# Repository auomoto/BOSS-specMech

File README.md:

# BOSS specMech
**_BOSS Spectrograph Mechanicals Controls for the LCO instrument_**

One of the two BOSS spectrographs will be moved to Las Campanas Observatory (LCO). Because existing spare parts inventory is not large enough to support two separate locations, we are replacing the obsolete items on the LCO instrument with currently available parts. One item is the microcontroller board, formerly a Z-World Little Giant, that is no longer manufactured (the original spectrograph was designed in the 1990s).

The new controller is built around a Microchip Curiosity Nano ATMega 4809. The source code and electronics schematics are here.

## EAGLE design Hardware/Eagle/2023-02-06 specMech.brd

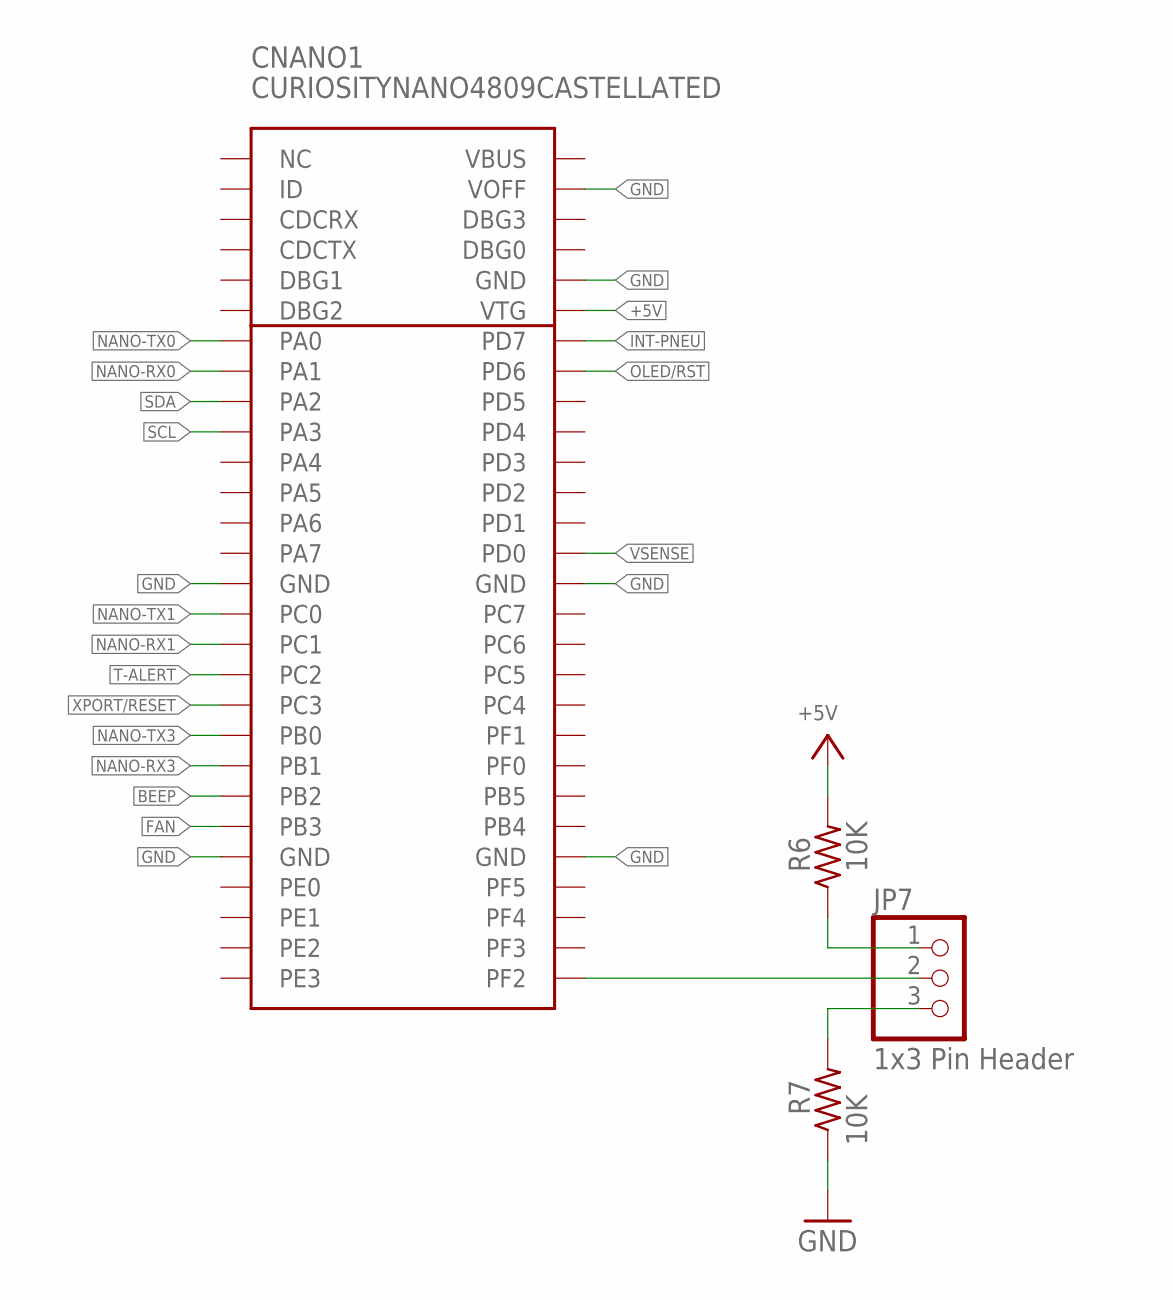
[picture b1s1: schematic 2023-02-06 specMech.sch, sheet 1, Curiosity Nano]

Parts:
CNANO1: CURIOSITYNANO4809CASTELLATED
JP7: 1x3 Pin Header; 1X03
R6, R7: 10K; R0805

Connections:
+5V: CNANO1.VTG, R6.2; also elsewhere on the board
BEEP: CNANO1.PB2; also elsewhere on the board
FAN: CNANO1.PB3; also elsewhere on the board
GND: CNANO1.GND15 (GND), CNANO1.GND24 (GND), CNANO1.GND33 (GND), CNANO1.GND42 (GND), CNANO1.GND52 (GND), CNANO1.VOFF, R7.1; also elsewhere on the board
INT-PNEU: CNANO1.PD7-AIN7 (PD7); also elsewhere on the board
unnamed: CNANO1.PF2, JP7.2
unnamed: JP7.3, R7.2
unnamed: JP7.1, R6.1
NANO-RX0: CNANO1.PA1-RX (PA1); also elsewhere on the board
NANO-RX1: CNANO1.PC1-RX (PC1); also elsewhere on the board
NANO-RX3: CNANO1.PB1-RX (PB1); also elsewhere on the board
NANO-TX0: CNANO1.PA0-TX (PA0); also elsewhere on the board
NANO-TX1: CNANO1.PC0-TX (PC0); also elsewhere on the board
NANO-TX3: CNANO1.PB0-TX (PB0); also elsewhere on the board
OLED/RST: CNANO1.PD6-AIN6 (PD6); also elsewhere on the board
SCL: CNANO1.PA3-SCL (PA3); also elsewhere on the board
SDA: CNANO1.PA2-SDA (PA2); also elsewhere on the board
T-ALERT: CNANO1.PC2; also elsewhere on the board
VSENSE: CNANO1.PD0-AIN0 (PD0); also elsewhere on the board
XPORT/RESET: CNANO1.PC3; also elsewhere on the board

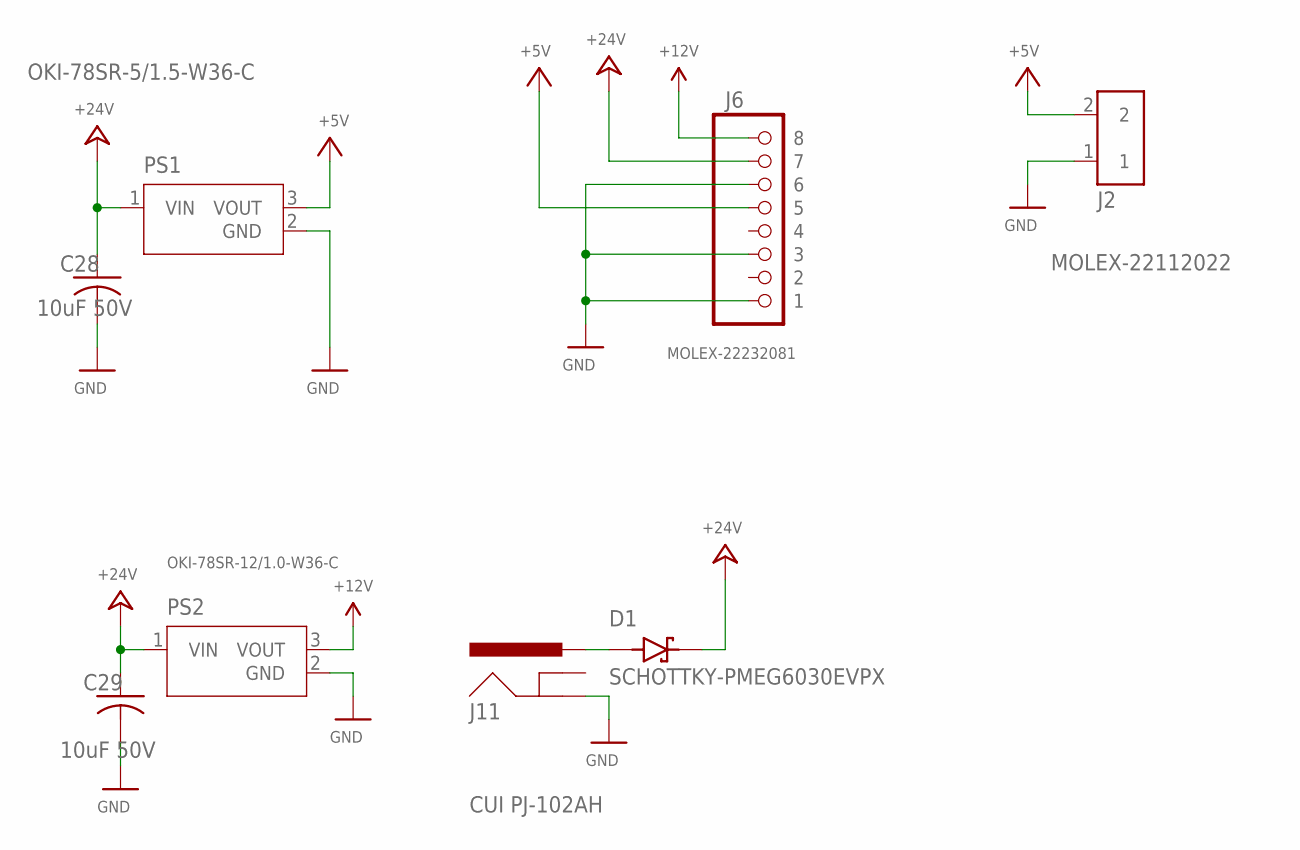
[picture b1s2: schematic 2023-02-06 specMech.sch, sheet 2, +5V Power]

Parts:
C28, C29: 10uF 50V; C1210
D1: SCHOTTKY-PMEG6030EVPX; DIO_PMEG6030EVPX
J2: MOLEX-22112022; 1X02-MOLEX-22112022
J6: MOLEX-22232081; 1X08-MOLEX-SHROUD
J11: CUI PJ-102AH; PJ-102AH
PS1: OKI-78SR-5/1.5-W36-C; CONV_OKI-78SR-5/1.5-W36-C
PS2: OKI-78SR-12/1.0-W36-C; CONV_OKI-78SR-5/1.5-W36-C

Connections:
+5V: J2.2, J6.P$5 (5), PS1.3 (VOUT); also elsewhere on the board
+12V: J6.P$8 (8), PS2.3 (VOUT); also elsewhere on the board
+24V: C28.1, C29.1, D1.1 (K), J6.P$7 (7), PS1.1 (VIN), PS2.1 (VIN); also elsewhere on the board
GND: C28.2, C29.2, J2.1, J6.P$1 (1), J6.P$3 (3), J6.P$6 (6), J11.GND, PS1.2 (GND), PS2.2 (GND); also elsewhere on the board
unnamed: D1.2 (A), J11.PWR

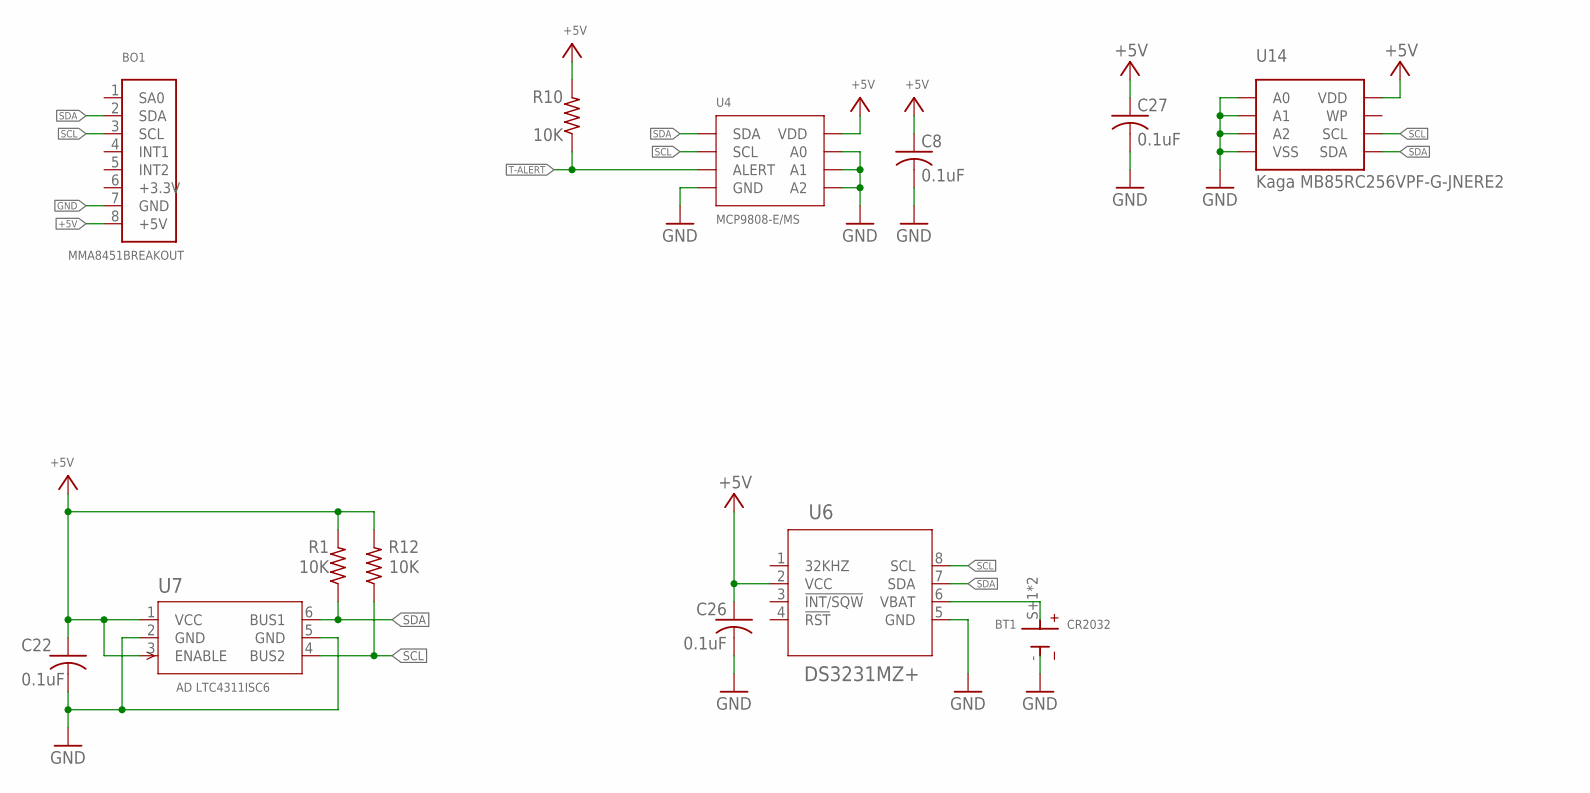
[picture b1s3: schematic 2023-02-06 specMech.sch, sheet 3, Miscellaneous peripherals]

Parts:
BO1: MMA8451BREAKOUT; 1X08
BT1: CR2032; BAT_BK-5058
C8, C22, C26, C27: 0.1uF; C0805
R1, R10, R12: 10K; R0805
U4: MCP9808-E/MS; MSOP8_MC_MCH
U6: DS3231MZ+; 21-0041B_8
U7: AD LTC4311ISC6; SOT-6_SC_LIT
U14: Kaga MB85RC256VPF-G-JNERE2; SOIC127P797X210-8N

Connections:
+5V: BO1.8 (+5V), C8.1, C22.1, C26.1, C27.1, R1.2, R10.2, R12.2, U4.8 (VDD), U6.2 (VCC), U7.1 (VCC), U7.3 (ENABLE), U14.8 (VDD); also elsewhere on the board
GND: BO1.7 (GND), BT1.-, C8.2, C22.2, C26.2, C27.2, U4.4 (GND), U4.5 (A2), U4.6 (A1), U4.7 (A0), U6.5 (GND), U7.2 (GND), U7.5 (GND), U14.1 (A0), U14.2 (A1), U14.3 (A2), U14.4 (VSS); also elsewhere on the board
SCL: BO1.3 (SCL), R12.1, U4.2 (SCL), U6.8 (SCL), U7.4 (BUS2), U14.6 (SCL); also elsewhere on the board
SDA: BO1.2 (SDA), R1.1, U4.1 (SDA), U6.7 (SDA), U7.6 (BUS1), U14.5 (SDA); also elsewhere on the board
T-ALERT: R10.1, U4.3 (ALERT); also elsewhere on the board
VBAT: BT1.S+1 (+), BT1.S+2 (+), U6.6 (VBAT)

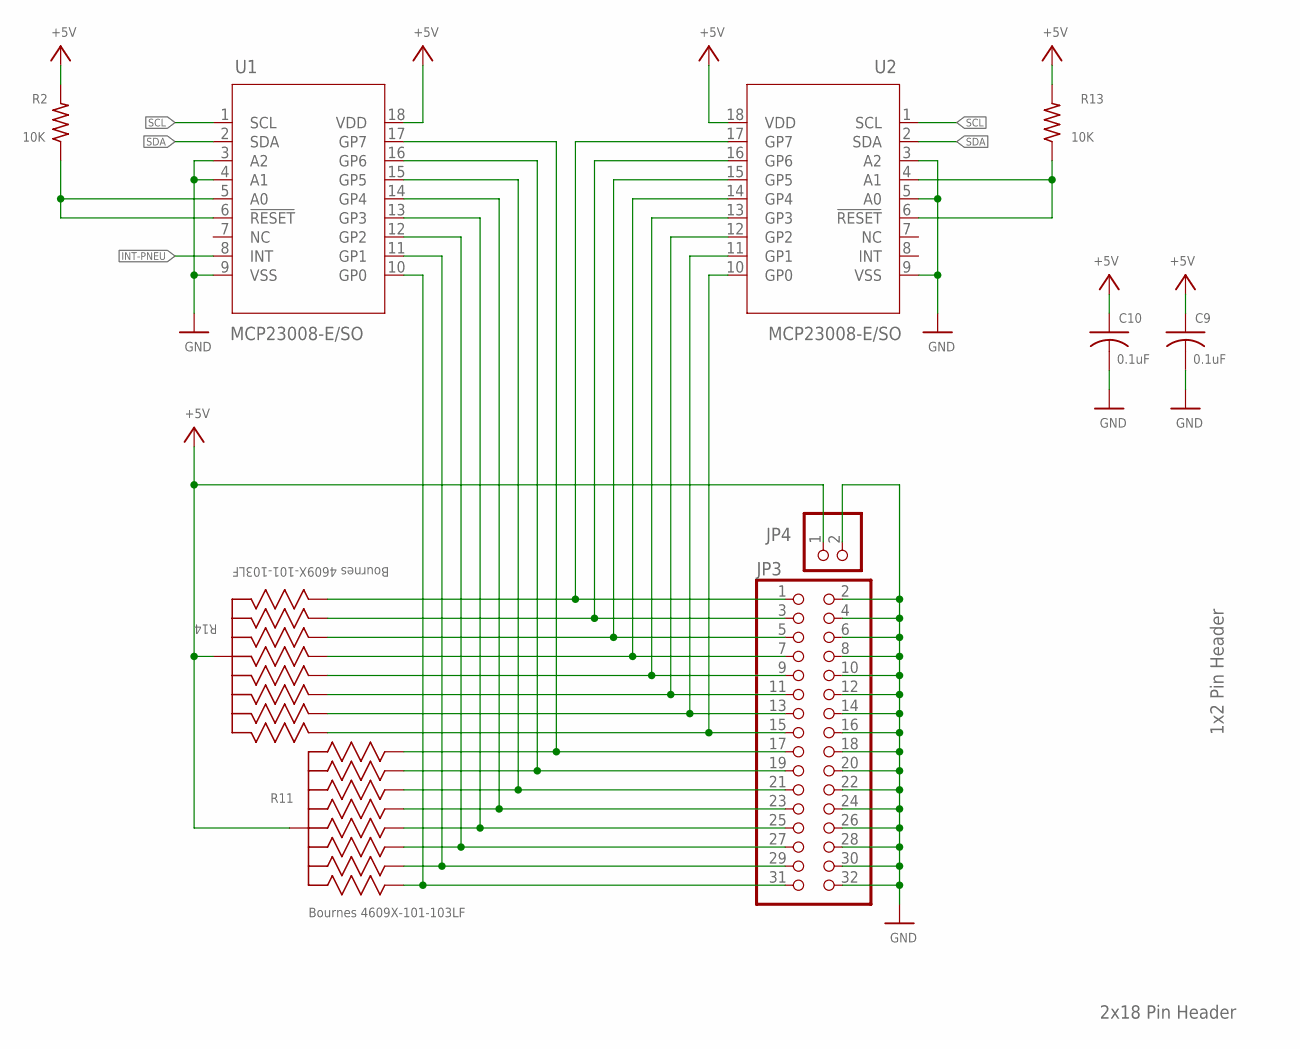
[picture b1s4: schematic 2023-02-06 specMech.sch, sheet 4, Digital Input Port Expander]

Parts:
C9, C10: 0.1uF; C0805
JP3: 2x18 Pin Header; 2X16
JP4: 1x2 Pin Header; 1X02
R2, R13: 10K; R0805
R11, R14: Bournes 4609X-101-103LF; BO_4609X
U1, U2: MCP23008-E/SO; SOIC18-W_MC

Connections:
+5V: C9.1, C10.1, JP4.1, R2.2, R11.1, R13.2, R14.1, U1.18 (VDD), U2.18 (VDD); also elsewhere on the board
GND: C9.2, C10.2, JP3.2, JP3.4, JP3.6, JP3.8, JP3.10, JP3.12, JP3.14, JP3.16, JP3.18, JP3.20, JP3.22, JP3.24, JP3.26, JP3.28, JP3.30, JP3.32, JP4.2, U1.3 (A2), U1.4 (A1), U1.9 (VSS), U2.3 (A2), U2.5 (A0), U2.9 (VSS); also elsewhere on the board
INT-PNEU: U1.8 (INT); also elsewhere on the board
unnamed: JP3.1, R14.2, U2.17 (GP7)
unnamed: JP3.3, R14.3, U2.16 (GP6)
unnamed: JP3.5, R14.4, U2.15 (GP5)
unnamed: JP3.7, R14.5, U2.14 (GP4)
unnamed: JP3.17, R11.9, U1.17 (GP7)
unnamed: JP3.19, R11.8, U1.16 (GP6)
unnamed: JP3.21, R11.7, U1.15 (GP5)
unnamed: JP3.23, R11.6, U1.14 (GP4)
unnamed: JP3.25, R11.5, U1.13 (GP3)
unnamed: R2.1, U1.5 (A0), U1.6 (!RESET)
unnamed: JP3.29, R11.3, U1.11 (GP1)
unnamed: JP3.31, R11.2, U1.10 (GP0)
unnamed: JP3.11, R14.7, U2.12 (GP2)
unnamed: JP3.27, R11.4, U1.12 (GP2)
unnamed: JP3.13, R14.8, U2.11 (GP1)
unnamed: JP3.15, R14.9, U2.10 (GP0)
unnamed: R13.1, U2.4 (A1), U2.6 (!RESET)
unnamed: JP3.9, R14.6, U2.13 (GP3)
SCL: U1.1 (SCL), U2.1 (SCL); also elsewhere on the board
SDA: U1.2 (SDA), U2.2 (SDA); also elsewhere on the board

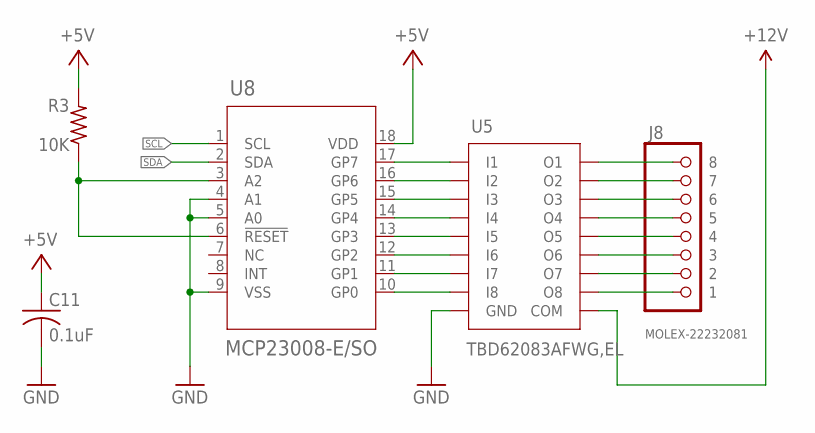
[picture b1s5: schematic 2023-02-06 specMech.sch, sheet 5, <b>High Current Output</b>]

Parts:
C11: 0.1uF; C0805
J8: MOLEX-22232081; 1X08-MOLEX-SHROUD
R3: 10K; R0805
U5: TBD62083AFWG,EL; SOIC127P1030X245-18
U8: MCP23008-E/SO; SOIC18-W_MC

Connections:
+5V: C11.1, R3.2, U8.18 (VDD); also elsewhere on the board
+12V: U5.10 (COM); also elsewhere on the board
GND: C11.2, U5.9 (GND), U8.4 (A1), U8.5 (A0), U8.9 (VSS); also elsewhere on the board
unnamed: U5.1 (I1), U8.17 (GP7)
unnamed: U5.2 (I2), U8.16 (GP6)
unnamed: U5.3 (I3), U8.15 (GP5)
unnamed: U5.4 (I4), U8.14 (GP4)
unnamed: U5.5 (I5), U8.13 (GP3)
unnamed: U5.6 (I6), U8.12 (GP2)
unnamed: U5.7 (I7), U8.11 (GP1)
unnamed: U5.8 (I8), U8.10 (GP0)
unnamed: R3.1, U8.3 (A2), U8.6 (!RESET)
unnamed: J8.P$8 (8), U5.18 (O1)
unnamed: J8.P$1 (1), U5.11 (O8)
unnamed: J8.P$2 (2), U5.12 (O7)
unnamed: J8.P$3 (3), U5.13 (O6)
unnamed: J8.P$4 (4), U5.14 (O5)
unnamed: J8.P$5 (5), U5.15 (O4)
unnamed: J8.P$6 (6), U5.16 (O3)
unnamed: J8.P$7 (7), U5.17 (O2)
SCL: U8.1 (SCL); also elsewhere on the board
SDA: U8.2 (SDA); also elsewhere on the board

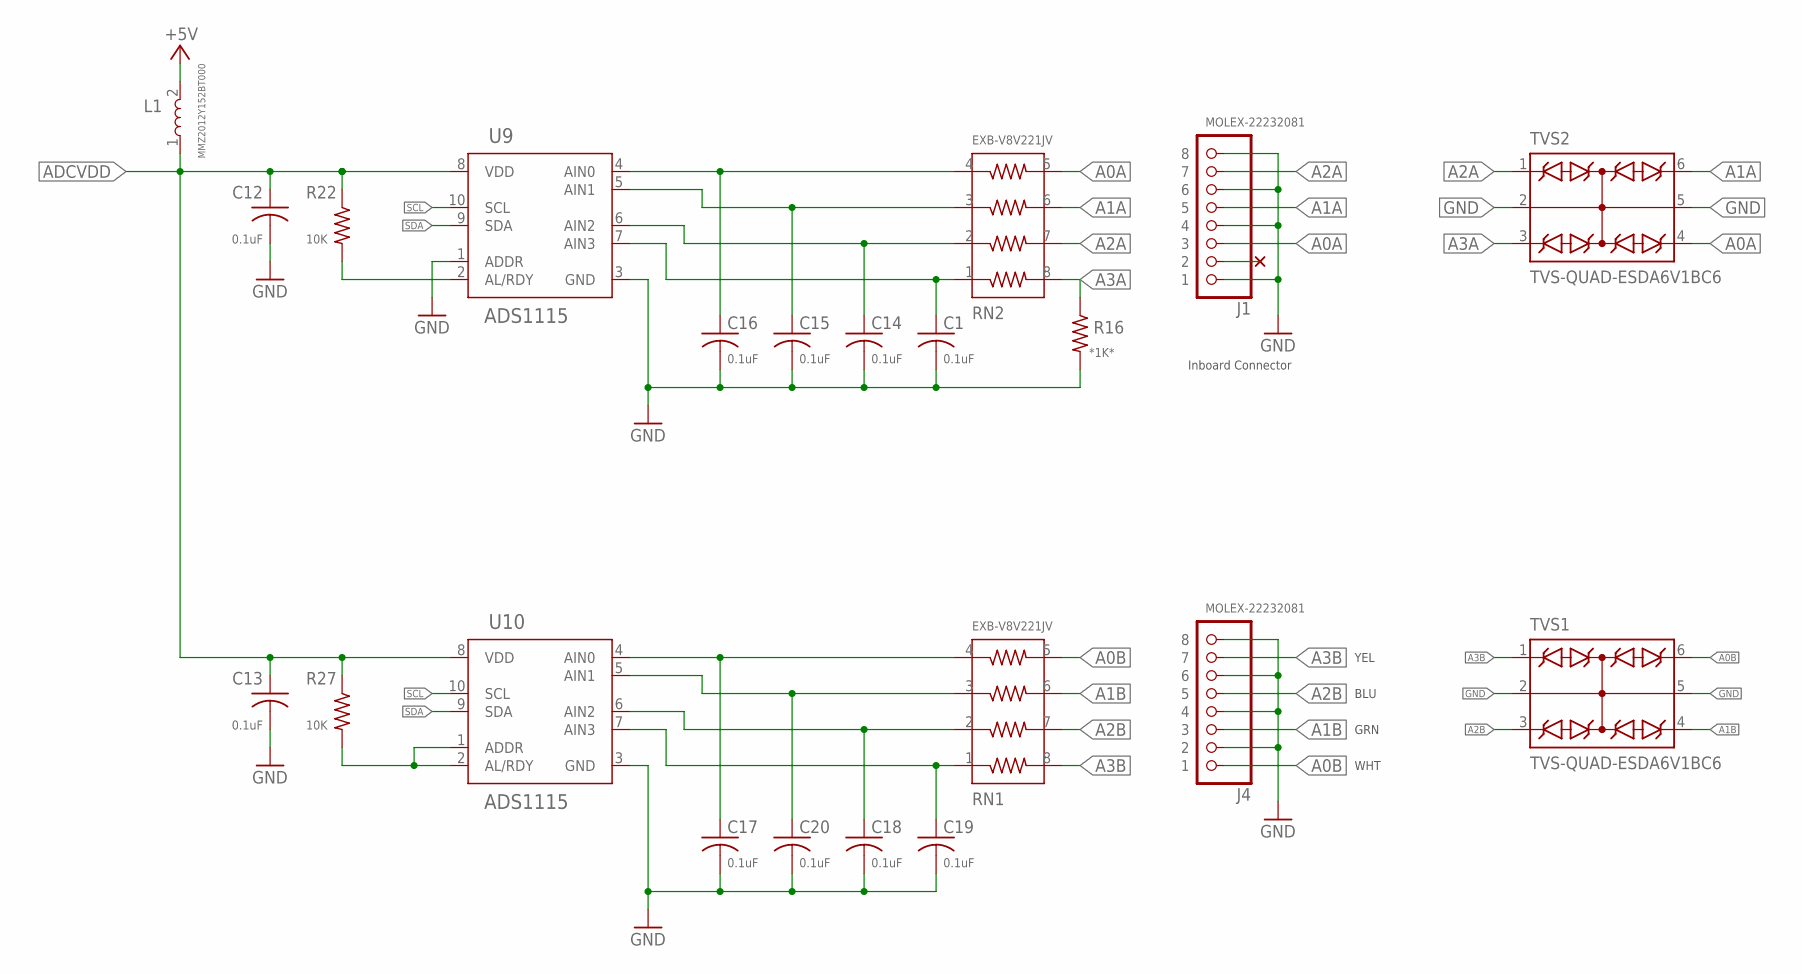
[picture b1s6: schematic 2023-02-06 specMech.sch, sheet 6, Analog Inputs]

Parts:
C1, C12, C13, C14, C15, C16, C17, C18, C19, C20: 0.1uF; C0805
J1, J4: MOLEX-22232081; 1X08-MOLEX-SHROUD
L1: MMZ2012Y152BT000; INDC2012X87N
R16: *1K*; R0805
R22, R27: 10K; R0805
RN1, RN2: EXB-V8V221JV; EXB38V_PAN
TVS1, TVS2: TVS-QUAD-ESDA6V1BC6; SOT95P280X145-6N
U9, U10: ADS1115; SOP50P490X110-10N

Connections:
+5V: L1.2; also elsewhere on the board
A0A: J1.P$3 (3), RN2.5, TVS2.4 (C3)
A0B: J4.P$1 (1), RN1.5, TVS1.6 (C4)
A1A: J1.P$5 (5), RN2.6, TVS2.6 (C4)
A1B: J4.P$3 (3), RN1.6, TVS1.4 (C3)
A2A: J1.P$7 (7), RN2.7, TVS2.1 (C1)
A2B: J4.P$5 (5), RN1.7, TVS1.3 (C2)
A3A: R16.1, RN2.8, TVS2.3 (C2); also elsewhere on the board
A3B: J4.P$7 (7), RN1.8, TVS1.1 (C1)
ADCVDD: C12.1, C13.1, L1.1, R22.1, R27.1, U9.8 (VDD), U10.8 (VDD); also elsewhere on the board
GND: C1.2, C12.2, C13.2, C14.2, C15.2, C16.2, C17.2, C18.2, C19.2, C20.2, J1.P$1 (1), J1.P$4 (4), J1.P$6 (6), J1.P$8 (8), J4.P$2 (2), J4.P$4 (4), J4.P$6 (6), J4.P$8 (8), R16.2, TVS1.2 (CC1), TVS1.5 (CC2), TVS2.2 (CC1), TVS2.5 (CC2), U9.1 (ADDR), U9.3 (GND), U10.3 (GND); also elsewhere on the board
unnamed: C1.1, RN2.1, U9.7 (AIN3)
unnamed: C16.1, RN2.4, U9.4 (AIN0)
unnamed: C15.1, RN2.3, U9.5 (AIN1)
unnamed: R22.2, U9.2 (AL/RDY)
unnamed: C19.1, RN1.1, U10.7 (AIN3)
unnamed: C14.1, RN2.2, U9.6 (AIN2)
unnamed: C18.1, RN1.2, U10.6 (AIN2)
unnamed: C20.1, RN1.3, U10.5 (AIN1)
unnamed: C17.1, RN1.4, U10.4 (AIN0)
unnamed: R27.2, U10.1 (ADDR), U10.2 (AL/RDY)
SCL: U9.10 (SCL), U10.10 (SCL); also elsewhere on the board
SDA: U9.9 (SDA), U10.9 (SDA); also elsewhere on the board

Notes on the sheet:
WHT
GRN
YEL
BLU
Inboard Connector

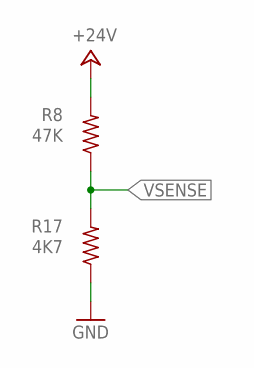
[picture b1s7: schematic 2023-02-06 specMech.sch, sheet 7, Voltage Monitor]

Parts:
R8: 47K; R0805
R17: 4K7; R0805

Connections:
+24V: R8.2; also elsewhere on the board
GND: R17.1; also elsewhere on the board
VSENSE: R8.1, R17.2; also elsewhere on the board

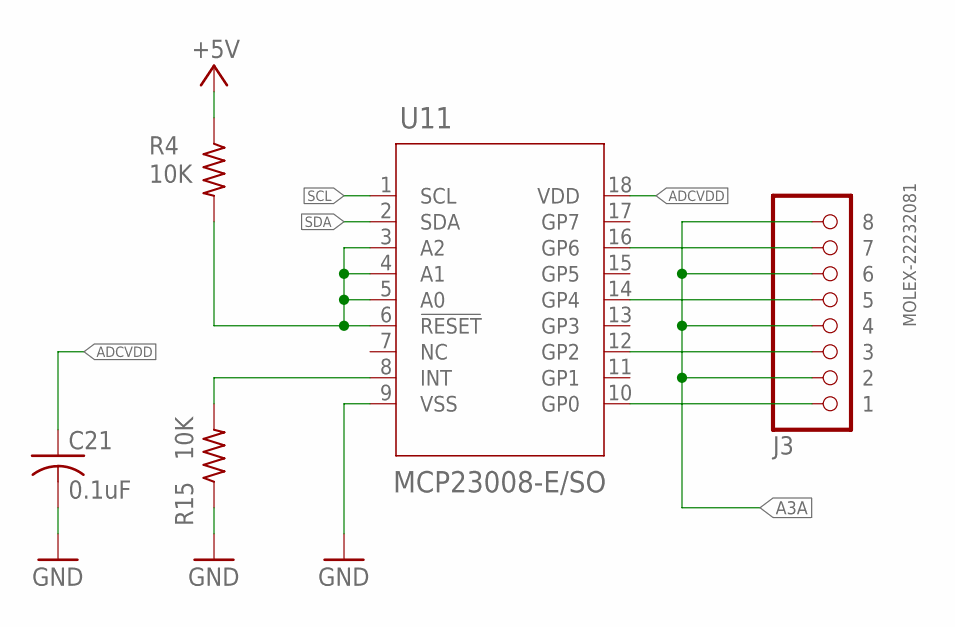
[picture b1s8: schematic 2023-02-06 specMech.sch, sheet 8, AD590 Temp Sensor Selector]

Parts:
C21: 0.1uF; C0805
J3: MOLEX-22232081; 1X08-MOLEX-SHROUD
R4, R15: 10K; R0805
U11: MCP23008-E/SO; SOIC18-W_MC

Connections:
+5V: R4.1; also elsewhere on the board
A3A: J3.P$2 (2), J3.P$4 (4), J3.P$6 (6), J3.P$8 (8); also elsewhere on the board
ADCVDD: C21.1, U11.18 (VDD); also elsewhere on the board
GND: C21.2, R15.1, U11.9 (VSS); also elsewhere on the board
unnamed: R4.2, U11.3 (A2), U11.4 (A1), U11.5 (A0), U11.6 (!RESET)
unnamed: R15.2, U11.8 (INT)
unnamed: J3.P$1 (1), U11.10 (GP0)
unnamed: J3.P$3 (3), U11.12 (GP2)
unnamed: J3.P$5 (5), U11.14 (GP4)
unnamed: J3.P$7 (7), U11.16 (GP6)
SCL: U11.1 (SCL); also elsewhere on the board
SDA: U11.2 (SDA); also elsewhere on the board

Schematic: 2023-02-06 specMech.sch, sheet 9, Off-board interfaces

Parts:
C2, C3, C23, C24, C25: 0.1uF; C0805
C4, C5: 0.01uF; C0805
C6: 10uF 50V; C1210
C7: 10uF 6V3; C0805
J7: Lantronix XPORT; XPORT-2
J9, J10: MOLEX-22112022; 1X02-MOLEX-22112022
J12: MOLEX-22112062; 1X06-MOLEX-22112062
JP1: 2x5 Pin Header; 2X05
JP2, JP5: 1x2 Pin Header; 1X02
JP6: Amphenol 75869-131LF; PINHD-2X3-SHROUDED
R5, R9: 10K; R0805
U3: TXB0102DCURVSSOP8; GHI-IC_VSSOP8(TI)
U12: 74HC2G17SOT457; SOP95P275X110-6
U13: ISO7421DR; SOIC127P599X175-8N
U15: SN74LV1T34DBVR; SOT95P280X145-5N
VR2: P7805-Q24-S3-S; CONV_P7805-Q24-S3-S

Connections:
+3.3V: C2.1, C4.1, C7.1, J7.3.3V (+3.3V), R9.2, U3.3 (VCCA), U15.5 (VCC), VR2.VOUT
+5V: C3.1, C23.1, C25.1, J12.6, JP1.8, JP2.2, JP6.3, U3.7 (VCCB), U12.5 (VCC), U13.8 (VCC2); also elsewhere on the board
+24V: C6.1, JP1.1, VR2.VIN; also elsewhere on the board
BEEP: J10.2; also elsewhere on the board
COLL-RX: JP1.3, U12.6 (1Y)
COLL-TX: JP1.7, U12.3 (2A)
CP3: J7.CP1, J7.CP2, J7.CP3, R5.2
FAN: J9.2; also elsewhere on the board
GND: C2.2, C3.2, C5.1, C6.2, C7.2, C23.2, C25.2, J7.GND, J9.1, J10.1, J12.5, JP1.2, JP1.5, JP1.9, JP5.2, JP6.2, JP6.5, R5.1, U3.2 (GND), U12.2 (GND), U13.5 (GND2), U15.3 (GND), VR2.GND; also elsewhere on the board
GND1: C24.2, J12.2, JP5.1, U13.4 (GND1)
GND-1: C4.2, C5.2, J7.P$1 (SH1), J7.P$2 (SH2)
INB: J12.1, U13.3 (INB)
unnamed: R9.1, U3.6 (OE)
NANO-RX0: U3.8 (B1); also elsewhere on the board
NANO-RX1: U12.4 (2Y); also elsewhere on the board
NANO-RX3: U13.6 (OUTB); also elsewhere on the board
NANO-TX0: U3.1 (B2); also elsewhere on the board
NANO-TX1: U12.1 (1A); also elsewhere on the board
NANO-TX3: U13.7 (INA); also elsewhere on the board
OLED/RST: JP6.4; also elsewhere on the board
OUTA: J12.3, U13.2 (OUTA)
SCL: JP6.6; also elsewhere on the board
SDA: JP6.1; also elsewhere on the board
VCC1: C24.1, J12.4, JP2.1, U13.1 (VCC1)
XP-RX: J7.RX, U3.4 (A2)
XP-TX: J7.TX, U3.5 (A1)
XP/RST: J7./RST, U15.4 (Y)
XPORT/RESET: U15.2 (A); also elsewhere on the board

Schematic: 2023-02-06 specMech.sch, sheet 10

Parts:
TP1, TP5: TP5000-TESTPOINT-BLK
TP2: TP5000-TESTPOINT-RED
TP3: TP5000-TESTPOINT-BLU
TP4: TP5000-TESTPOINT-YEL
TP6, TP7: TP5000-TESTPOINT-ORG

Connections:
+5V: TP2.P$1; also elsewhere on the board
+24V: TP6.P$1; also elsewhere on the board
GND: TP1.P$1, TP5.P$1; also elsewhere on the board
SCL: TP4.P$1; also elsewhere on the board
SDA: TP3.P$1; also elsewhere on the board
VSENSE: TP7.P$1; also elsewhere on the board

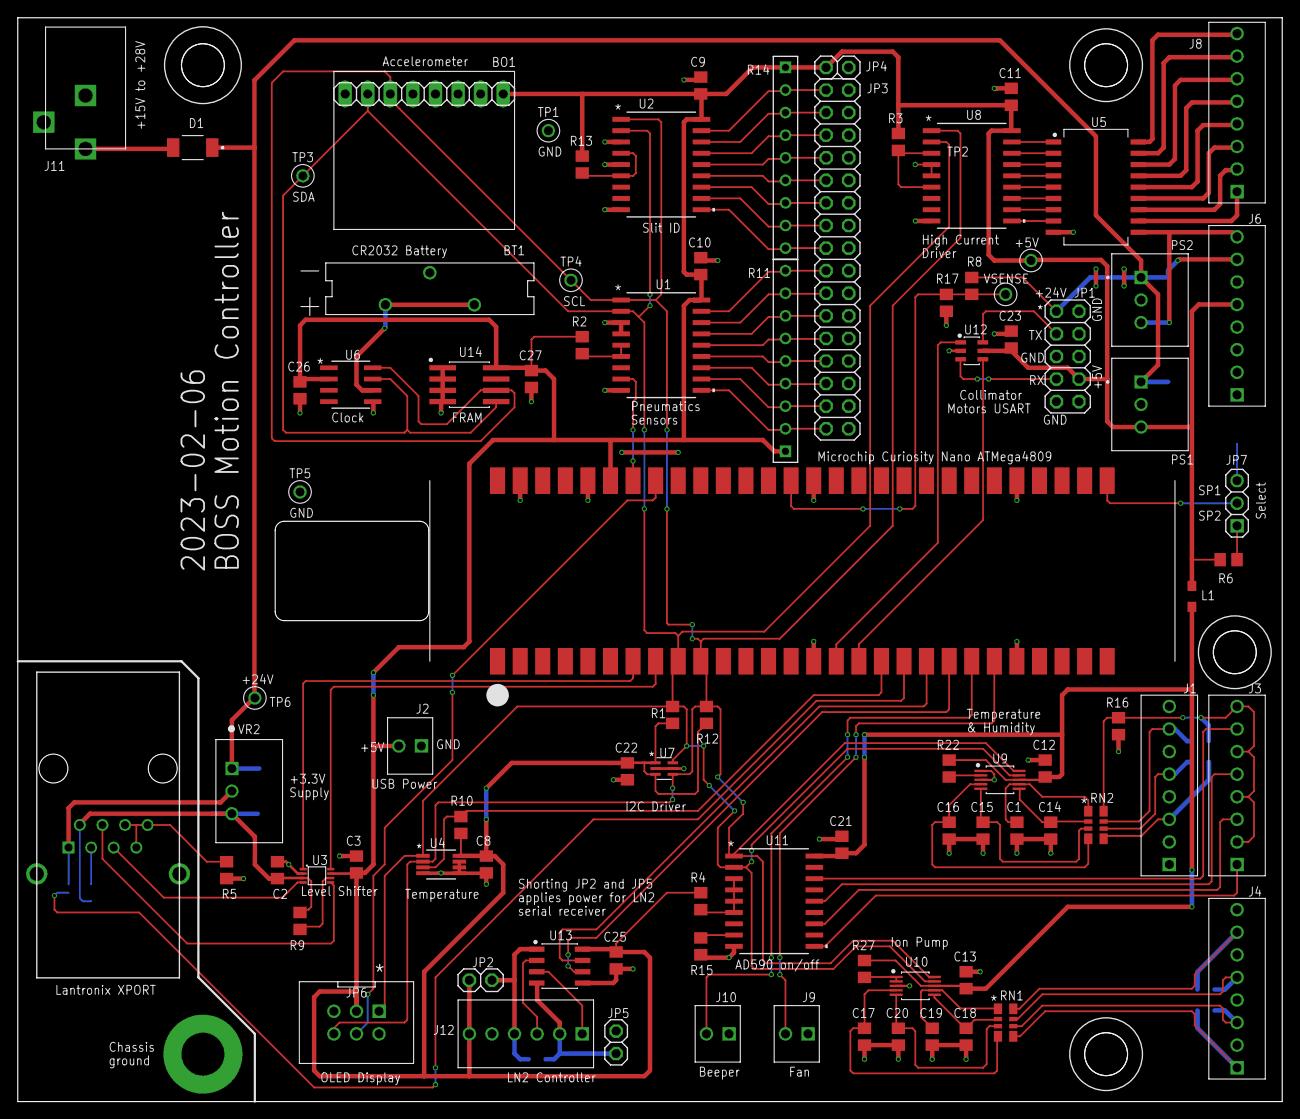
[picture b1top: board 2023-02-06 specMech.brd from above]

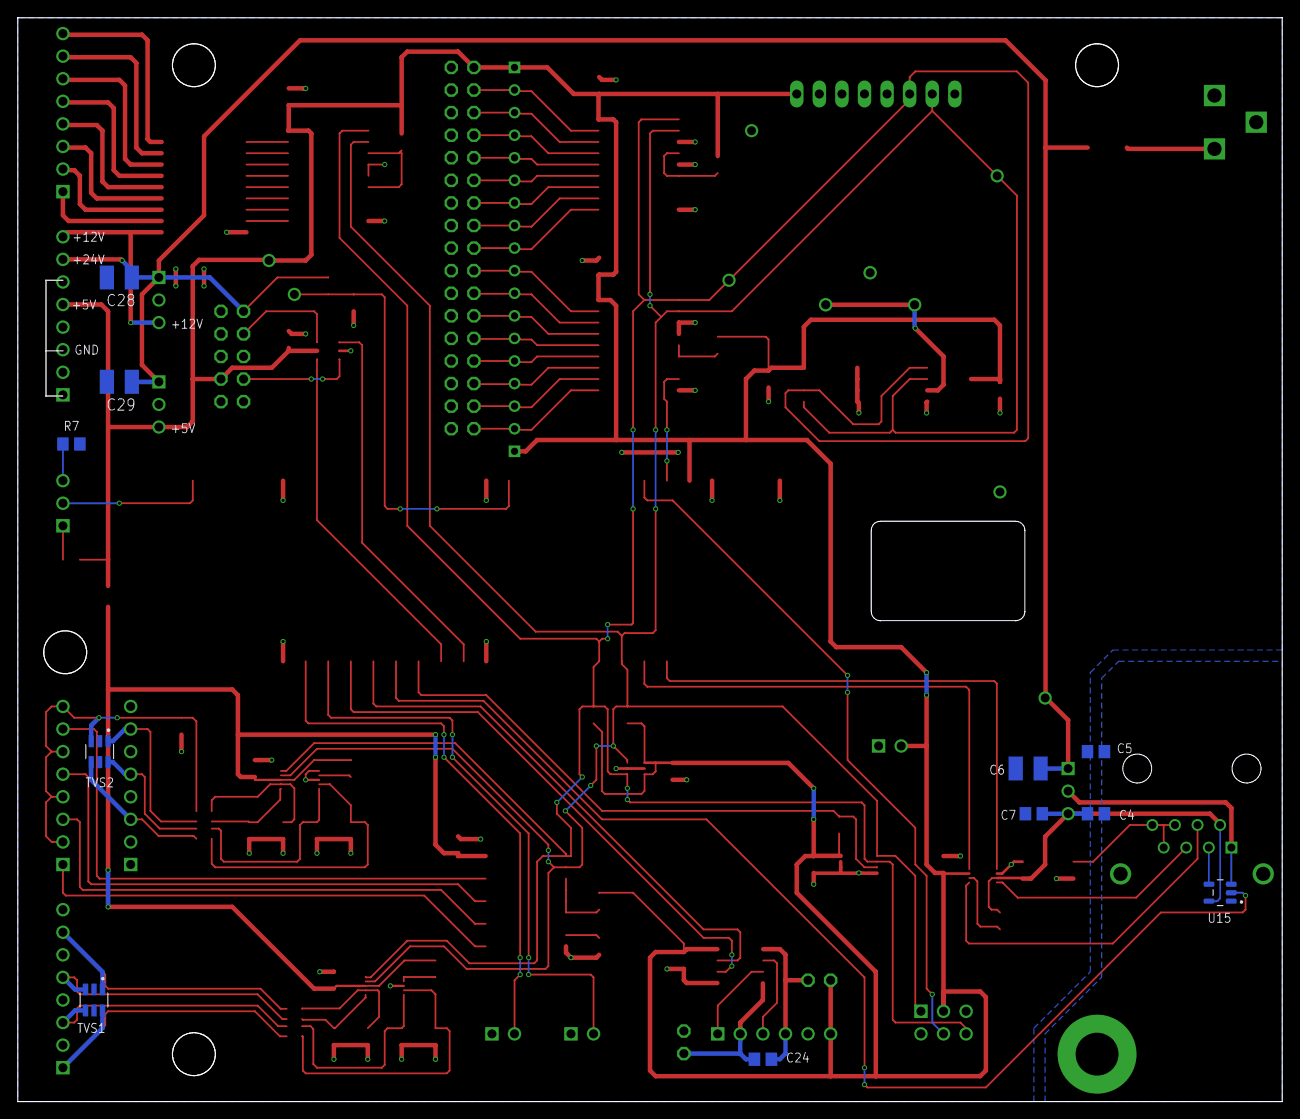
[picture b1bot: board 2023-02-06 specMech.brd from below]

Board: 2 copper layers, 142.2 x 121.9 mm, 100 parts (11 on the bottom side), 97 nets.

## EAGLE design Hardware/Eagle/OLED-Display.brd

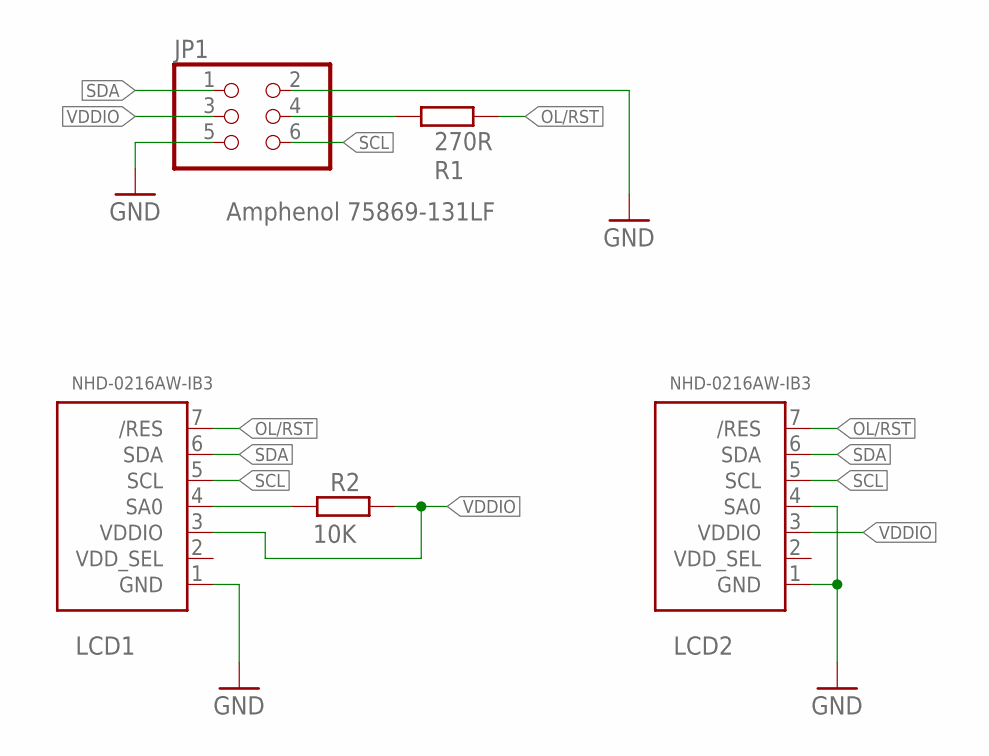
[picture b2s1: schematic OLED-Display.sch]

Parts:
JP1: Amphenol 75869-131LF; PINHD-2X3-SHROUDED
LCD1, LCD2: NHD-0216AW-IB3; LCD-NEWHAVEN-16X2
R1: 270R; R0805
R2: 10K; R0805

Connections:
ADDR1: LCD1.4 (SA0), R2.1
GND: JP1.2, JP1.5, LCD1.1 (GND), LCD2.1 (GND), LCD2.4 (SA0)
OL/RST: LCD1.7 (/RES), LCD2.7 (/RES), R1.2
RESET: JP1.4, R1.1
SCL: JP1.6, LCD1.5 (SCL), LCD2.5 (SCL)
SDA: JP1.1, LCD1.6 (SDA), LCD2.6 (SDA)
VDDIO: JP1.3, LCD1.3 (VDDIO), LCD2.3 (VDDIO), R2.2

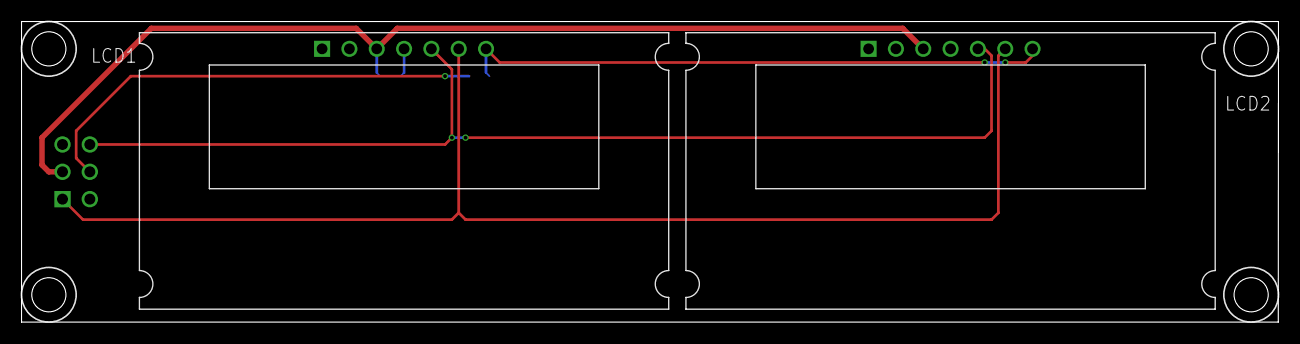
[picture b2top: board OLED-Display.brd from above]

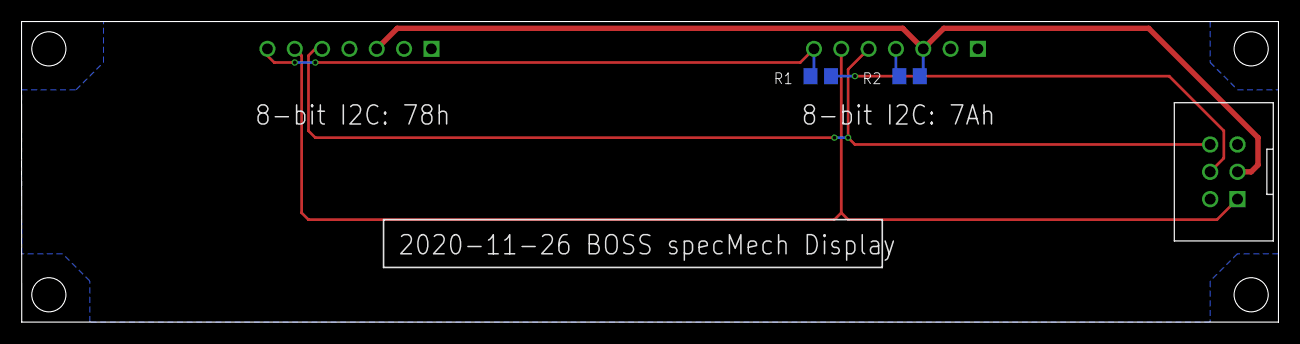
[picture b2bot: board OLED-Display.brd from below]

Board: 2 copper layers, 116.8 x 27.9 mm, 5 parts (3 on the bottom side), 7 nets.

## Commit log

2020-10-19 BOSS Mechanical Controls
    Atmel Studio 7 software runs on a Curiosity Nano ATMega4809 to control the BOSS spectrograph mechanical items and sensors.
2020-10-19 specMech
    BOSS spectrograph mechanicals software
2020-10-19 Set theme jekyll-theme-slate
2020-10-19 Set theme jekyll-theme-minimal
2020-10-19 removed theme
2020-10-19 Added Eagle schematic and board files
    These are far from final.
2020-10-21 Worked on board layout
2020-10-26 Remove backup Eagle files
2020-10-27 Started XPORT placement
2020-10-28 Fixed level shifter orientation
2020-10-29 Change name to include BOSS
2020-10-30 Added Schmitt trigger to RoboClaw interface
2020-10-30 Added RTC & battery
2020-10-30 Rearranged parts on board
2020-11-01 Removed XPORT hole over pad, general cleanup
2020-11-01 ADC area layout improvements
2020-11-01 Add shorting jumper to ADC ground
2020-11-01 Removed errant character at end of brd file
2020-11-01 Rearrange ADC chips after brd file recovery
2020-11-01 Rearranging parts
2020-11-01 Added ADC ground plane
2020-11-01 Routed high current lines
2020-11-01 Wiring
2020-11-04 Fixed accelerometer footprint
2020-11-04 Connected pneumatic sensor interrupt
2020-11-04 Added Ground Overpasses
2020-11-04 Moved wire for USB port clearance on Nano board
2020-11-06 Partitioned grounds (removed analog ground)
2020-11-06 Updated board label
2020-11-06 Enlarged USB connector clearance hole
2020-11-06 Problem pushing to fusion
2020-11-06 Reverting to change label time
2020-11-06 Used later version of XPORT-2
2020-11-07 Finish for the day
2020-11-07 Connected VOFF to GND
2020-11-09 Added +5V power for USB isolator (JST 2-pin header)
2020-11-09 Changed FRAM footprint to allow both IC sizes
2020-11-10 Added spectrograph selection jumper
2020-11-10 Fixed label errors in humidity sensor input lines
2020-11-10 Added test points, changed conflicting i2c address
2020-11-11 Added some part values, changed date on label
2020-11-11 Added cutout for USB connector, cleaned up some traces
2020-11-12 Submitted this one (Rev0) for fab to Oshpark
    2020-11-12 specMech Rev0
2020-11-18 Moved shim thickness text
2020-11-18 Added future change notes to schematic
2020-11-19 Removed old backup files
2020-11-26 Added OLED-Display
2020-11-27 Added pullup note to schematic
2020-12-12 Printed 2020-11-12 Schematic
2020-12-15 Made copy of 2020-11-12 version
2020-12-26 Recover Github error?
2020-12-27 Removed EOD line
2020-12-27 Modified FRAM routines for new TWI code
2020-12-27 Cleaned up comments and in-line documentation
2020-12-29 Wrote ADS1115 routine, not tested
2021-01-02 Re-did the ADC and AD590 routines
2021-01-02 Commented main.c and added PROMPT defines
2021-01-02 Updated comments in all files
2021-01-04 Set up differential ADC for Ion Pump readout
2021-01-05 Cleaned up ion pump routine, verified operation
2021-01-05 Minor edits
2021-01-13 Removed timezone (Z) from reported times
2021-01-14 Updated docs to match the code
2021-01-14 Fixed formatting error in format_ERR
2021-01-19 OLED Display minor mods
2021-01-24 Removed Eagle backup files
2021-01-24 Edited comments
2021-01-25 Added command ID to the loop
    Added a command parsing routine, pulling the command pieces out into a new structure. This is to create a command identifier that can be carried with every instance of a command.
2021-01-25 Cmd loop mods for more commands
2021-01-25 Removed commented routines
2021-01-25 Removed error mesg on empty <CR>
2021-01-26 Starting major changes
    Moved ferrite bead
2021-01-26 Swapped castellated board in, starting rerouting
2021-01-26 More routing
2021-01-27 More routing, mostly OK now
2021-01-27 Molex 1x2 header replaces JST header
2021-01-27 Added TVS diodes on ADC inputs
2021-01-27 Moved the accelerometer a bit away from board edge
2021-01-31 Accelerometer small mods
2021-02-06 Started testing OLED display
2021-02-06 Enabled button to reboot
2021-02-06 Set up RTC for flashing led
2021-02-07 globals.h failure
2021-02-07 fail globals.h
2021-02-07 Recover
2021-02-07 fail
2021-02-07 Revert
2021-02-07 undoing
2021-02-08 Re-loaded everything into a new Atmel Studio project
2021-02-08 Updated part number for high current driver
2021-02-08 USB Cutout in board bigger; software debugging
2021-02-09 Pneumatics interrupt detected, display improvements
2021-02-10 Changed LN2 connector pinout to swap rx & tx
2021-02-13 Added fan control
2021-02-14 Changed to 7-bit TWI addresses everywhere
2021-02-17 Forced rebootack to be !<CR> EXACTLY
2021-02-17 Removed boottime command (rB)
2021-02-18 Added XPort reset & changed OLED display connector
2021-02-20 Added 10uF cap on 5V dc-dc input
2021-02-22 Labeled Fan connector
2021-02-22 separated uart tracks a bit
2021-02-23 Made a copy today
2021-02-24 trying to fix the hacking problem; clamped input buffer overflow
2021-02-24 Recompiled with XPort reset on reboot
2021-02-27 Renamed USART lines to match Curiosity designations
2021-02-28 2021-02-28 backup copy made
2021-03-01 Added timer TCB0 routines
2021-03-02 Started adding RoboClaw. Read main volts OK in testroutine
2021-03-04 Added motor encoder, speed, and current readout
2021-03-06 Roboclaw motion commands
2021-03-07 Clean up the code
2021-03-08 Partly cleaned up roboclaw & made a copy
2021-03-09 Cleaned up RoboClaw routines
2021-03-10 More RoboClaw improvements (catching errors)
2021-03-10 Clean up RoboClaw routines
2021-03-11 More cleanup; still needs work
2021-03-16 Undid some Roboclaw bad attempts
2021-03-17 Added save to FRAM motor encoder routine (not tested)
2021-03-17 Added getFRAM_MOTOREncoder (not tested)
2021-03-17 Another try at killing the hacker RDP attack
2021-03-17 This doesn't work
2021-03-22 Added motor encoder FRAM storage
2021-03-25 Removed read-before-write on saving motor encoder value
2021-03-30 Cleaned up initialization sequence
2021-04-20 Minor board edits
2021-04-21 Saved 2021-04-21 version
2021-04-22 Added 24V sense line
2021-04-22 Connected MCP9808 temp sensor alert line
2021-05-20 Made 2021-04-22 copy for build
2021-05-27 Updates before ordering
2021-07-24 Second version
2021-11-10 Added to office GitHub repository
2021-11-21 Save latest
2021-11-23 Fixed motor runaway and pneumatics reads
2021-11-24 move_MOTORAbsolute doesn't work
2021-11-25 9600 baud (doesn't work at 38400 anymore?)
2021-11-25 Consolidating motor routines
2021-11-25 More cleanup
2021-11-26 Removed get_MOTOREncoder, replaced with get_MOTOR_ENCODER
2021-11-26 Replaced get_MOTORFloat with get_MOTOR_FLOAT
2021-11-26 Cleanup PID routines
2021-11-26 Save the 2021-11-26 version
2021-11-28 Added PID report to rA, rB, rC
2021-11-28 Added max current routines, tuned Portescap PID to new current limits
2021-11-30 Added qpps write; still problems with cmd 74 (S4MODE write)
2021-11-30 Added motor ID to error reports
2021-11-30 Cleaned up roboclaw.c formatting
2021-12-02 Started homing routine development
2021-12-09 General save
2021-12-12 Save yesterday's copy
2021-12-13 Removed circular buffer on USART1, added stop command
2021-12-17 Motor working again; interim state
2021-12-18 Minor cleanup; motors still work
2021-12-22 Improved serial connection to motor; seems reliable now
2021-12-23 Clean up roboclaw.c
2021-12-24 Cleanup
2021-12-24 Added init_PNEU to initialize()
2022-04-24 Added get_MOTOR_LIMIT (not tested)
2022-04-25 Added limit switch and motor direction code
2022-04-30 added limit switch recovery (unstick)
2022-05-01 Added new motor PD parameter files
2022-05-01 Added Motion Studio screenshots
2022-05-05 Minor edits on RoboClaw code
2022-05-05 Newly measured PID parameters into roboclaw.h
2022-05-06 New PID, unsafe and safe cmds
2022-05-09 Faster RoboClaw & TWI speeds
2022-05-21 Added beeper and fan routines
2022-05-24 Minor experiments, no changes
2022-05-24 Cleaned up hardware backup copies
2022-05-27 rebuilt w/o changes
2022-05-30 Debugging LN2 section
2022-05-31 LN2 report reformat, added timestamp
2022-06-13 PS voltage readout, fan state added
2022-07-21 Minor edits?
2023-02-06 Added power to LN2 serial connection
